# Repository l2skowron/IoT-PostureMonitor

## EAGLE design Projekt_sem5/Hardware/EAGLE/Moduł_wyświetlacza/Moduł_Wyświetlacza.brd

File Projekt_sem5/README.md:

# Nakładka na fotel monitorująca postawę użytkownika

### Autor: Łukasz Skowron
### Projekt: Nakładka na fotel monitorująca postawę użytkownika

## Opis Projektu
Projekt składa się z dwóch modułów opartych na układach ESP32, 
których zadaniem jest analiza nacisku wywieranego przez użytkownika na oparcie i siedzisko fotela.
System informuje użytkownika o błędnej postawie za pomocą interfejsu graficznego oraz sygnalizacji świetlnej (LED).

### Kluczowe Funkcje:
* **Pomiar wielopunktowy**: Wykorzystanie 3 czujników FSR oraz 4 czujników tensometrycznych.
* **Komunikacja Bezprzewodowa**: Protokół ESP-NOW - brak potrzeby kabla komunikacyjnego).
* **Inteligentna Kalibracja**: Możliwość zdefiniowania prawidłowej postawy oraz jej zapis do pamięci nieulotnej NVS.
* **Interfejs UI**: Wizualizacja obciążenia poszczególnych sekcji fotela na wyświetlaczu.

### Architektura:
* **Nadajnik (ESP32-C3)**: Zbieranie danych z czujników i transmisja radiowa.
* **Odbiornik (ESP32-S3)**: Analiza danych, obsługa wyświetlacza, diod oraz zarządzanie kalibracją.

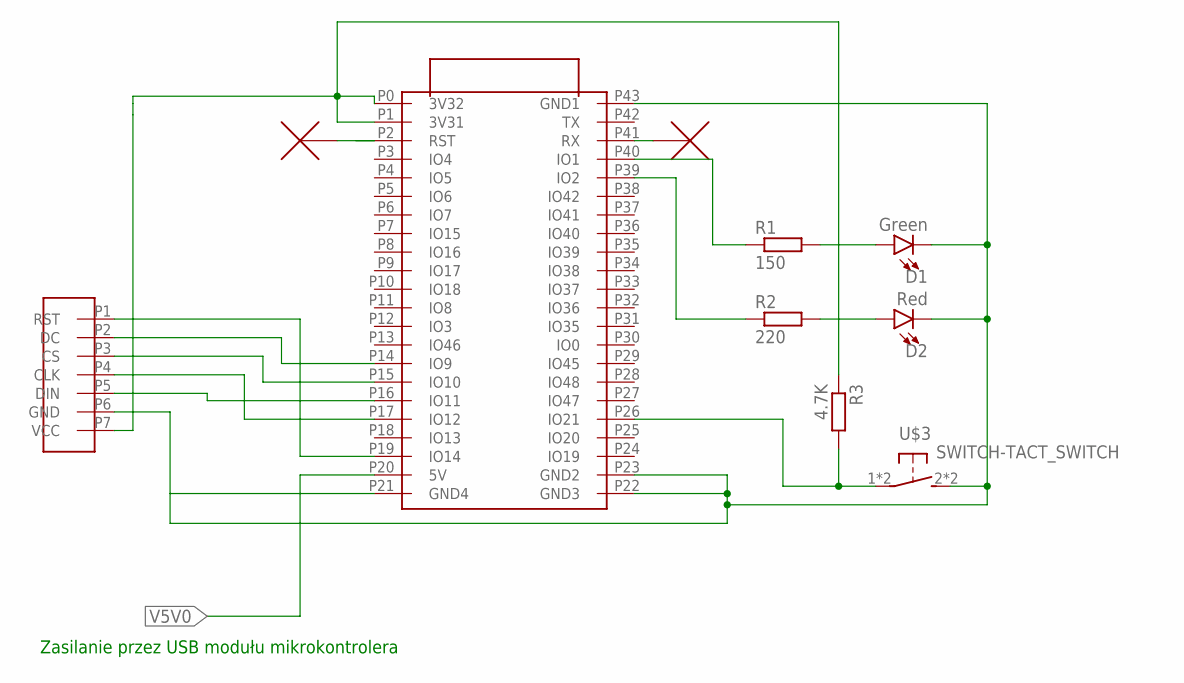
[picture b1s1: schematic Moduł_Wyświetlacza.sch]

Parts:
D1: Green; SPARKFUN-LED_LED_5MM
D2: Red; SPARKFUN-LED_LED_5MM
R1: 150; 0204/7
R2: 220; 0204/7
R3: 4.7K; 0204/7
U$1: PROJEKT_SE5_ESP32-S3-DEVKIT
U$2: PROJEKT_SE5_OLED_MODULE; PROJEKT_SE5_1.5INC_RGB_OLED
U$3: SWITCH-TACT_SWITCH; SWITCH-TACT_DTSM-6

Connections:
unnamed: D1.K (C), D2.K (C), U$1.P21 (GND4), U$1.P22 (GND3), U$1.P23 (GND2), U$1.P43 (GND1), U$2.P6 (GND), U$3.2, U$3.4 (2)
unnamed: U$1.P19 (IO14), U$2.P1 (RST)
unnamed: U$1.P14 (IO9), U$2.P2 (DC)
unnamed: U$1.P15 (IO10), U$2.P3 (CS)
unnamed: U$1.P17 (IO12), U$2.P4 (CLK)
unnamed: U$1.P16 (IO11), U$2.P5 (DIN)
unnamed: R3.2, U$1.P26 (IO21), U$3.1, U$3.3 (1)
unnamed: D2.A, R2.2
unnamed: D1.A, R1.2
unnamed: R1.1, U$1.P40 (IO1)
unnamed: R2.1, U$1.P39 (IO2)
unnamed: R3.1, U$1.P0 (3V32), U$1.P1 (3V31), U$2.P7 (VCC)
V5V0: U$1.P20 (5V)

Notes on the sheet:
Zasilanie przez USB modułu mikrokontrolera

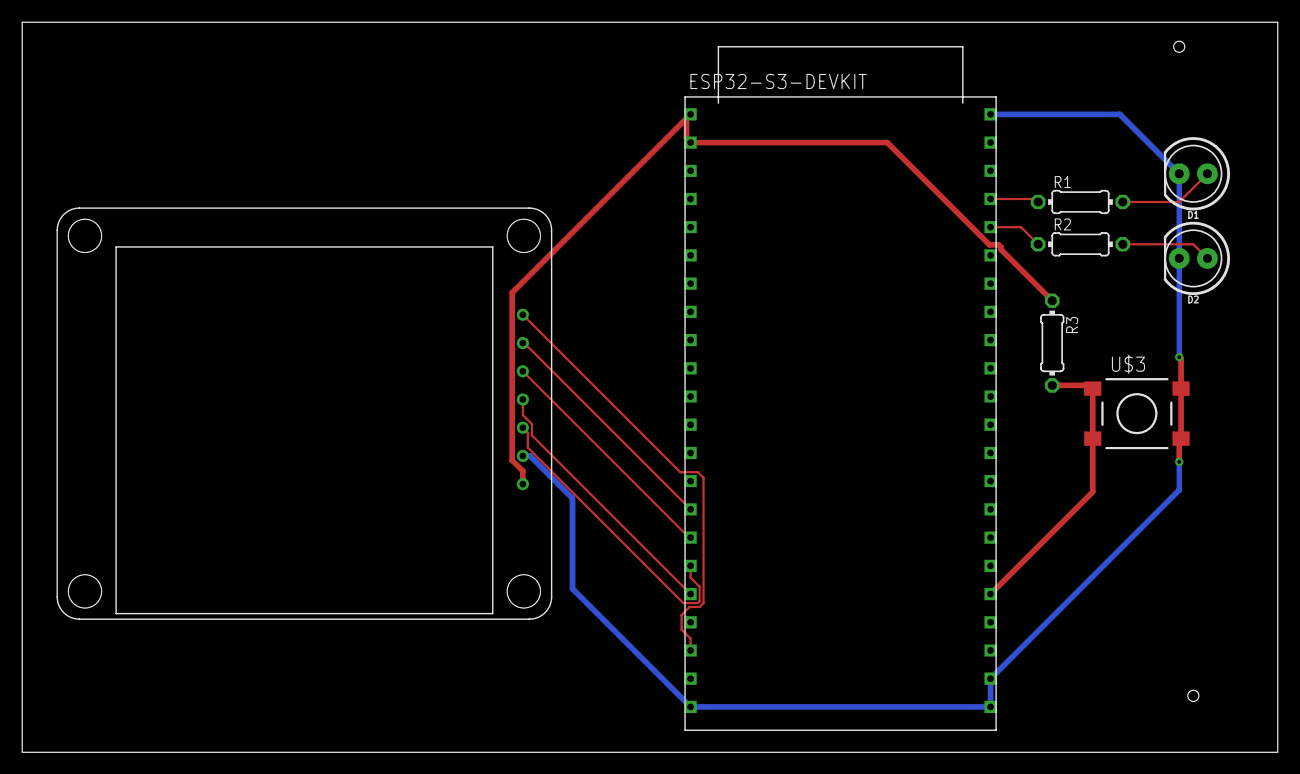
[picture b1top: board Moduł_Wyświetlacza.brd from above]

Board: 2 copper layers, 113.0 x 65.7 mm, 8 parts (0 on the bottom side), 12 nets.

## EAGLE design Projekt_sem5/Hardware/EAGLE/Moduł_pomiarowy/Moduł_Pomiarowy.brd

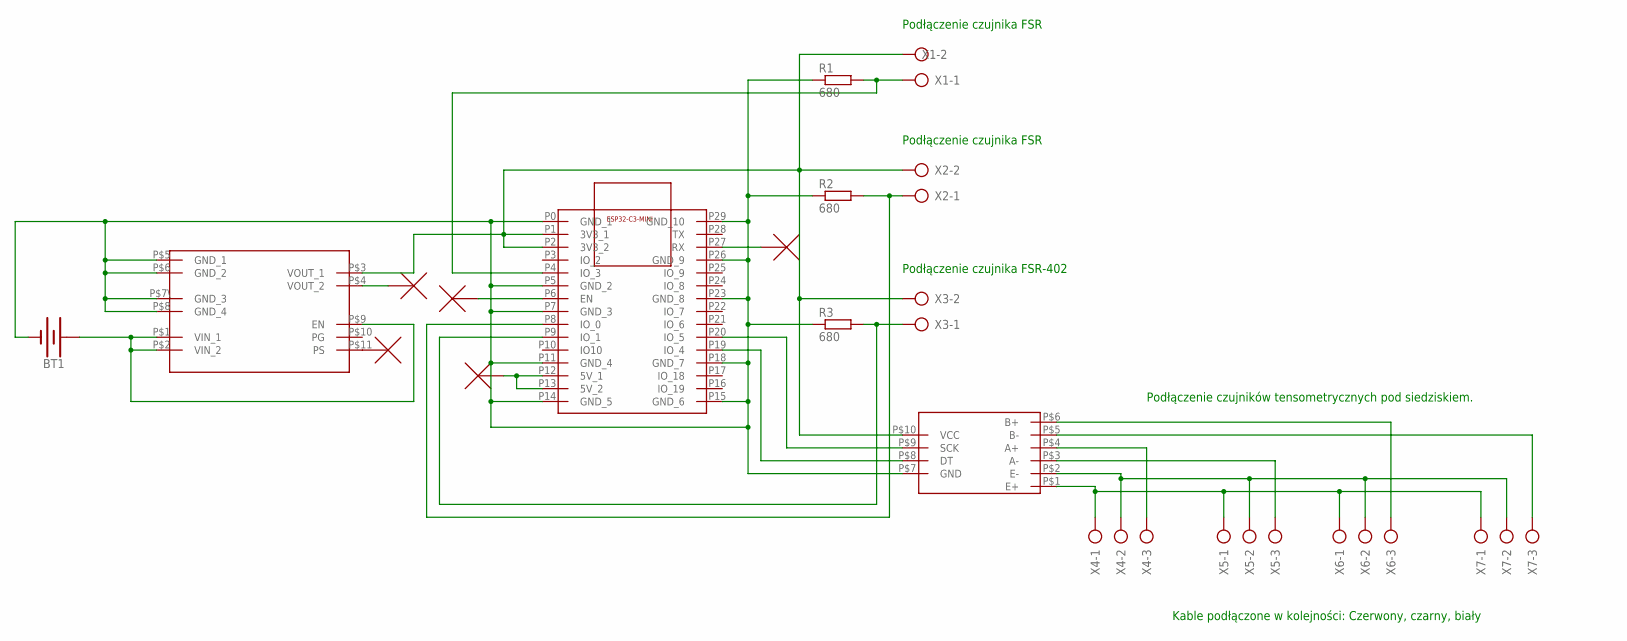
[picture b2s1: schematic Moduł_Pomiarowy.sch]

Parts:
BT1: SPARKFUN-BATTERIES_BATTERY-AA
R1, R2, R3: 680; 0207/10
U$1: PROJEKT_SE5_ESP32-C3-MINI-DEVKITESP32-C3-MINI; PROJEKT_SE5_ESP32-C3-MINI
U$2: PROJEKT_SE5_XFW-HX711; PROJEKT_SE5_XFV-HX711
U$3: PROJEKT_SE5_TPS63020-MODULE; PROJEKT_SE5_TPS63020
X1, X2, X3: AK300/2
X4, X5, X6, X7: AK300/3

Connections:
GND: BT1.GND@1 (-), R1.1, R2.1, R3.1, U$1.P0 (GND_1), U$1.P5 (GND_2), U$1.P7 (GND_3), U$1.P11 (GND_4), U$1.P14 (GND_5), U$1.P15 (GND_6), U$1.P18 (GND_7), U$1.P23 (GND_8), U$1.P26 (GND_9), U$1.P29 (GND_10), U$2.P$7 (GND), U$3.P$5 (GND_1), U$3.P$6 (GND_2), U$3.P$7\ (GND_3), U$3.P$8 (GND_4)
unnamed: BT1.PWR@1 (+), U$3.P$1 (VIN_1), U$3.P$2 (VIN_2), U$3.P$9 (EN)
unnamed: U$2.P$1 (E+), X4.1, X5.1, X6.1, X7.1
unnamed: U$2.P$2 (E-), X4.2, X5.2, X6.2, X7.2
unnamed: U$1.P1 (3V3_1), U$1.P2 (3V3_2), U$2.P$10 (VCC), U$3.P$3 (VOUT_1), X1.2, X2.2, X3.2
unnamed: U$2.P$4 (A+), X4.3
unnamed: U$2.P$3 (A-), X5.3
unnamed: U$2.P$6 (B+), X6.3
unnamed: R2.2, U$1.P8 (IO_0), X2.1
unnamed: R3.2, U$1.P9 (IO_1), X3.1
unnamed: R1.2, U$1.P4 (IO_3), X1.1
unnamed: U$2.P$5 (B-), X7.3
unnamed: U$1.P20 (IO_5), U$2.P$9 (SCK)
unnamed: U$1.P19 (IO_4), U$2.P$8 (DT)
unnamed: U$1.P12 (5V_1), U$1.P13 (5V_2)

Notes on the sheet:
Podłączenie czujnika FSR
Podłączenie czujnika FSR-402
Podłączenie czujników tensometrycznych pod siedziskiem.
Kable podłączone w kolejności: Czerwony, czarny, biały

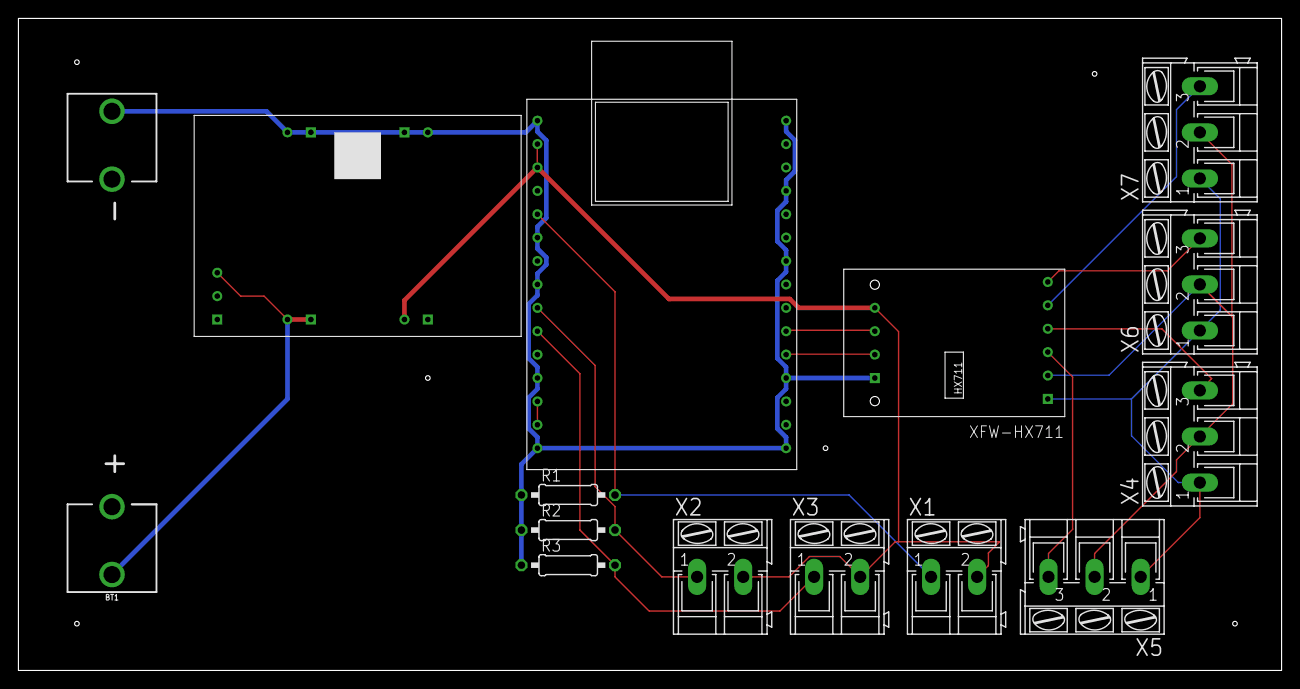
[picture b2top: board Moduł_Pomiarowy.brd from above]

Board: 2 copper layers, 137.1 x 70.8 mm, 14 parts (0 on the bottom side), 15 nets.

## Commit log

2026-03-30 Microcontrolers IoT System
    Fully working microporessor-based device that monitors spinal posture in real-time using FSR and tensometric sensor and provides a visual feedback.
